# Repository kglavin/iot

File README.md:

# iot
various pieces of iot experimentation including
* micropython
* esp8266 featherboard

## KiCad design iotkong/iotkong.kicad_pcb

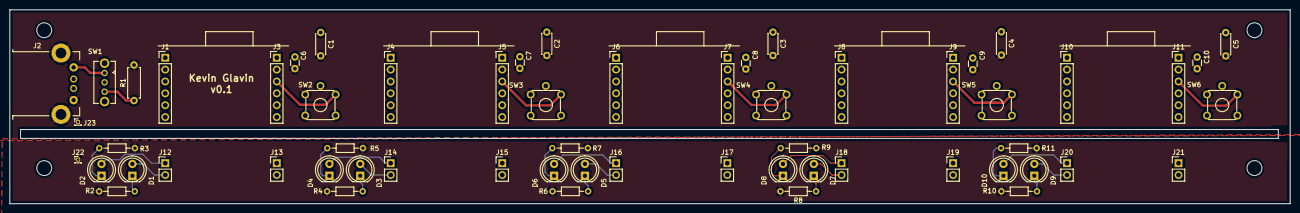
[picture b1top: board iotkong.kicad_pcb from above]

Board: 2 copper layers, 274.1 x 41.5 mm, 64 parts (0 on the bottom side), 29 nets.

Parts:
C1, C2, C3, C4, C5: 47uF; C_Disc_D4.3mm_W1.9mm_P5.00mm
C6, C7, C8, C9, C10: 0.1uF; C_Disc_D3.0mm_W1.6mm_P2.50mm
D1, D2, D3, D4, D5, D6, D7, D8, D9, D10: LED; LED_D5.0mm
J1, J3, J4, J5, J6, J7, J8, J9, J10, J11: Conn_01x06_Female; PinHeader_1x06_P2.54mm_Vertical
J2: USB_B; USB_2_0
J12, J13, J14, J15, J16, J17, J18, J19, J20, J21: Conn_01x06_Female; PinHeader_1x02_P2.54mm_Vertical
J22, J23: Conn_01x01_Female; PinHeader_1x01_P1.00mm_Vertical
MH1, MH2, MH3, MH4: MountingHole; MountingHole_3.2mm_M3_ISO7380
R1: 100; R_Axial_DIN0207_L6.3mm_D2.5mm_P7.62mm_Horizontal
R2, R3, R4, R5, R6, R7, R8, R9, R10, R11: 100; R_Axial_DIN0204_L3.6mm_D1.6mm_P7.62mm_Horizontal
SW1: SW_Push_SPDT; CKN10397-ND
SW2, SW3, SW4, SW5, SW6: SW_SPST; SW_TH_Tactile_Omron_B3F-10xx

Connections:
GND: C1.2, C2.2, C3.2, C4.2, C5.2, C6.2, C7.2, C8.2, C9.2, C10.2, J1.2, J2.4, J2.5, J3.2, J4.2, J5.2, J6.2, J7.2, J8.2, J9.2, J10.2, J11.2, J22.1, J23.1, R1.2, R2.2, R3.2, R4.2, R5.2, R6.2, R7.2, R8.2, R9.2, R10.2, R11.2, SW2.1, SW3.1, SW4.1, SW5.1, SW6.1
LED1: D2.2, J12.1
LED2: D1.2, J12.2
LED3: D4.2, J14.1
LED4: D3.2, J14.2
LED5: D6.2, J16.1
LED6: D5.2, J16.2
LED7: D8.2, J18.1
LED8: D7.2, J18.2
LED9: D10.2, J20.1
LED10: D9.2, J20.2
unnamed: D1.1, R2.1
unnamed: D2.1, R3.1
unnamed: D3.1, R4.1
unnamed: D4.1, R5.1
unnamed: D5.1, R6.1
unnamed: D6.1, R7.1
unnamed: D7.1, R8.1
unnamed: D8.1, R9.1
unnamed: D9.1, R10.1
unnamed: D10.1, R11.1
unnamed: J2.1, SW1.1
unnamed: J3.3, SW2.2
unnamed: J5.3, SW3.2
unnamed: J7.3, SW4.2
unnamed: J9.3, SW5.2
unnamed: J11.3, SW6.2
unnamed: R1.1, SW1.3
VCC: C1.1, C2.1, C3.1, C4.1, C5.1, C6.1, C7.1, C8.1, C9.1, C10.1, J3.1, J5.1, J7.1, J9.1, J11.1, SW1.2

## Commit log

2018-08-31 get rid of .DS_Store on mac
2018-08-31 setup micropython dir structure
2018-09-01 basic fake stats from iot device via http post
2018-09-03 working with flask/json and config loop
2018-09-03 ran for 1000 loop
2018-09-06 job machine to allow for a downloaded list of tasks to be executed.
2018-09-07 inheritance structure
2018-09-08 first cut at multi module board
2018-09-08 silkscreening
2018-09-08 running on other 8266 board, runing the job_machine also
2018-09-08 pipout for hiletgo -703681358704 board
2018-09-09 0.98 alignment for board
2018-09-09 runnable on micropython and a second device id
2018-09-11 added leds and board pinout details
2018-09-12 added leds and placed
2018-09-13 fixed switches
2018-09-14 updated foorprints
2018-09-14 additional datasheet
2018-09-19 seperated board to top and bottom
